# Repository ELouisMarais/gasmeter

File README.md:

# gasmeter
Raspberry Pi based reader for pulse output gasmeters.
The content you seek is in the 'develop' branch.

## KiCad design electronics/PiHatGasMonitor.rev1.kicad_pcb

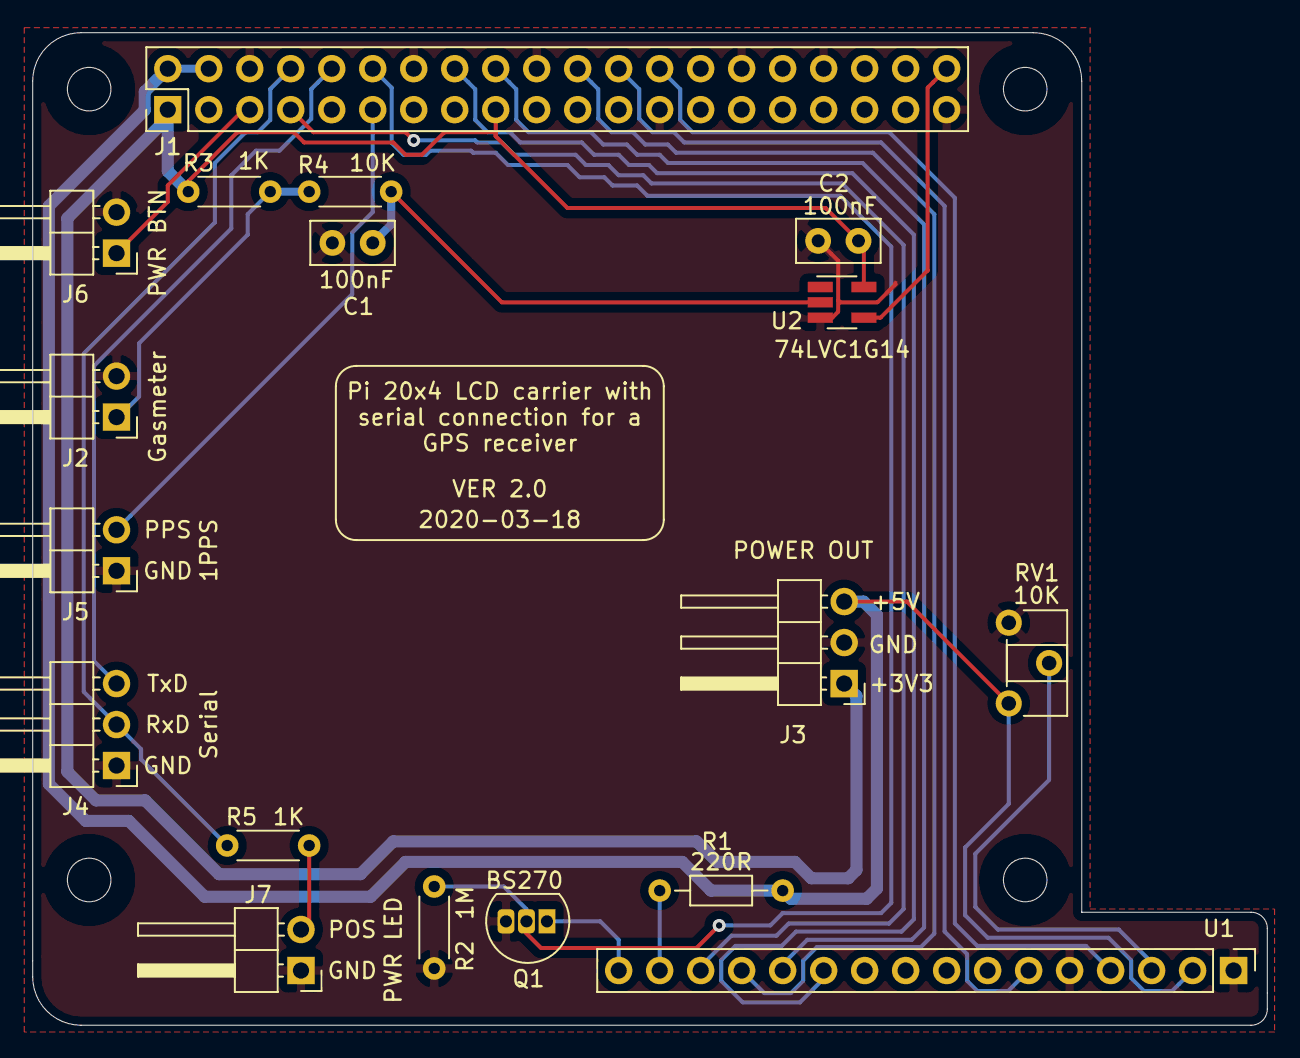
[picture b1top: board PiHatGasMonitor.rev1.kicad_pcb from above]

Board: 2 copper layers, 76.5 x 61.5 mm, 22 parts (0 on the bottom side), 21 nets.

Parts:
C1, C2: 100N; C_Disc_D5.0mm_W2.5mm_P2.50mm
J1: Raspberry_Pi_2_3_4; PinHeader_2x20_P2.54mm_Vertical
J2: Gasmeter; PinHeader_1x02_P2.54mm_Horizontal
J3: Power OUT; PinHeader_1x03_P2.54mm_Horizontal
J4: Serial; PinHeader_1x03_P2.54mm_Horizontal
J5: 1PPS in; PinHeader_1x02_P2.54mm_Horizontal
J6: POWER BTN; PinHeader_1x02_P2.54mm_Horizontal
J7: PWR LED; PinHeader_1x02_P2.54mm_Horizontal
M1, M2, M3, M4: MountingHole_2.7mm_M2.5
Q1: BS270; TO-92L_Inline
R1: 220R; R_Axial_DIN0204_L3.6mm_D1.6mm_P7.62mm_Horizontal
R2: 1M; R_Axial_DIN0204_L3.6mm_D1.6mm_P5.08mm_Horizontal
R3, R5: 1K; R_Axial_DIN0204_L3.6mm_D1.6mm_P5.08mm_Horizontal
R4: 10K; R_Axial_DIN0204_L3.6mm_D1.6mm_P5.08mm_Horizontal
RV1: 10K; Potentiometer_ACP_CA6-H2,5_Horizontal
U1: LCD_4x20; PinHeader_1x16_P2.54mm_Vertical
U2: 74LVC1G14; SOT-23-5_HandSoldering

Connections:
+3V3: C2.1, J1.1, J1.17, J3.1, R3.1, U2.5
+5V: J1.2, J1.4, J3.3, R1.1, RV1.3, U1.2
GND: C1.2, C2.2, J1.6, J1.9, J1.14, J1.20, J1.25, J1.30, J1.34, J1.39, J2.2, J3.2, J4.1, J5.1, J6.2, J7.1, Q1.3, R2.2, RV1.1, U1.1, U1.5, U2.3
unnamed: C1.1, R4.1, U2.2
unnamed: J1.5, J6.1
unnamed: J1.7, U1.14
unnamed: J1.8, J4.2, R5.2
unnamed: J1.10, J4.3
unnamed: J1.11, J5.2
unnamed: J1.12, Q1.2, R2.1
unnamed: J1.16, U1.11
unnamed: J1.18, U1.12
unnamed: J1.22, U1.13
unnamed: J1.24, U1.6
unnamed: J1.26, U1.4
unnamed: J1.40, U2.4
unnamed: J2.1, R3.2, R4.2
unnamed: J7.2, R5.1
unnamed: Q1.1, U1.16
unnamed: R1.2, U1.15
unnamed: RV1.2, U1.3

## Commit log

2018-12-20 Initial commit of c and c++ files
2018-12-20 Initial commit of Python files
2018-12-20 Minor change to the build script
2020-09-23 New versions of broadcast and recvmsg scripts
2020-09-23 Added a document describing the use of the broadcast and recvmsg scripts
2021-07-07 Complete redo, most software now in Python 3.
2021-07-07 Added instructions for setting up the software on the Pi
2021-07-07 Updated setup document
2021-07-07 Added electronics and enclosure files
2021-07-07 Updated software set up document
2021-07-08 A test
2021-07-08 Deleted test file
2021-07-08 Alternative PCB with connectors moved inwards
2021-07-08 Modified broadcast software, updated documentation, fixed bug in build script
2021-07-09 Updated recvmsg software
2021-07-12 Tiny bugs fixed
2021-08-19 Added intensity.c file. I deleted it earlier by mistake.
2021-08-19 Updated documentation
2026-01-12 Fixed issue with dependencies in intensity.c
2026-01-14 Many additions and some small fixes
2026-01-14 Code changes to prevent excessive data sent to file due to delayed time of day synchronisation
2026-01-15 Changed way time steps are calculated - precaution for unsynchronised time of day
2026-01-22 added service file for intensity application
2026-01-23 Updated UPS software - added a file with lines for the LCD display
2026-01-27 Bug fix
2026-01-27 Made "build" executable
2026-01-28 Added UPS messaging to the gasmeter application
2026-02-25 Added a check for a large change in time-of-day
